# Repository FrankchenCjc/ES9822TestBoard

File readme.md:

# 关于本项目

本项目的电路设计来自ES9822的DataSheet，并使用了LM1117进行电压控制，目前版本还未进行试机

请使用kicad6.0及以上版本的kicad打开该项目
## ES9xxx符号库和器件库的问题
kicad6适用的ES9xxx的符号库还在制作，目前不打算开源

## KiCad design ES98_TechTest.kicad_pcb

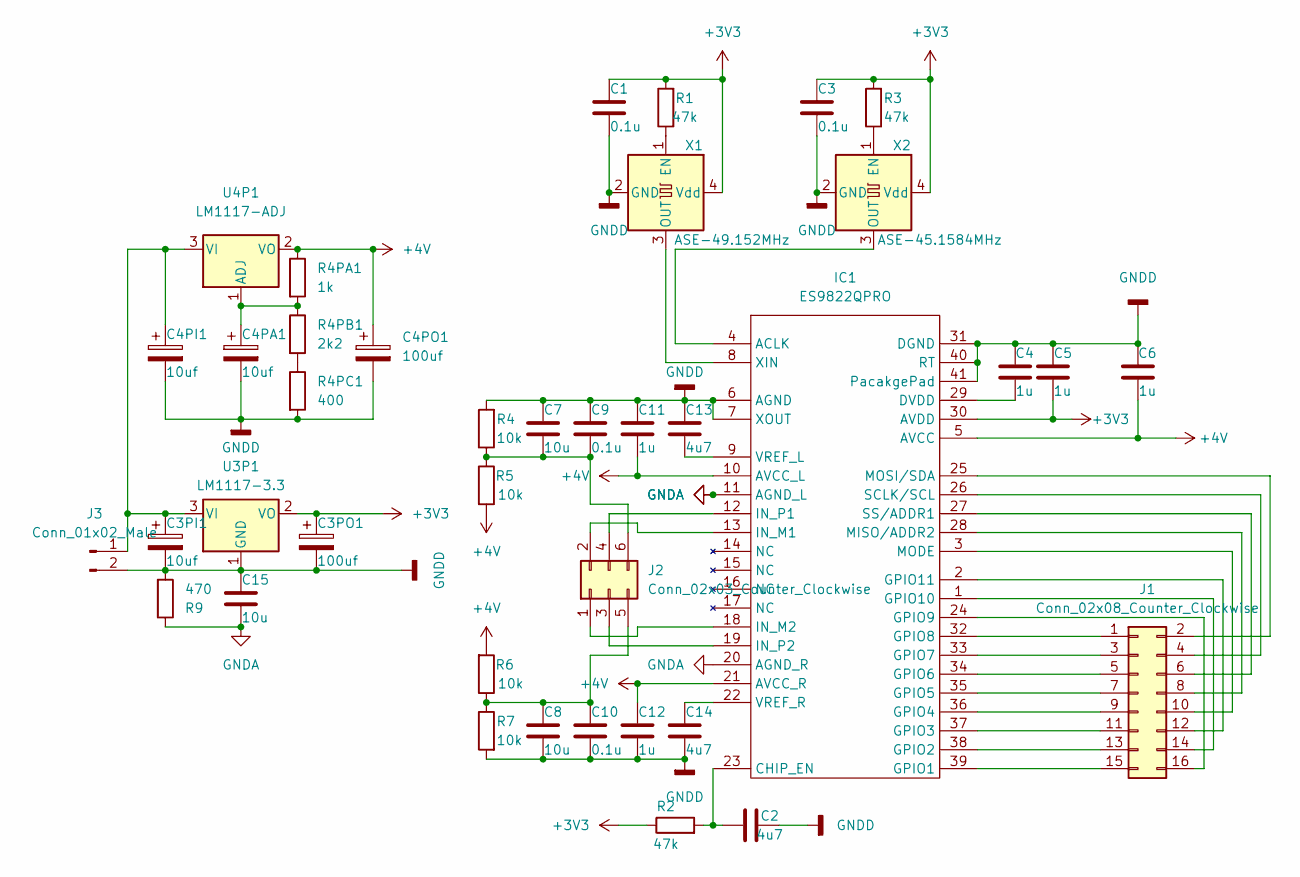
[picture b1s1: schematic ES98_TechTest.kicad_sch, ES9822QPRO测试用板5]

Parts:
C1, C3, C9, C10: 0.1u; C_0603_1608Metric_Pad1.08x0.95mm_HandSolder
C2, C13, C14: 4u7; C_0603_1608Metric_Pad1.08x0.95mm_HandSolder
C3PI1, C4PA1, C4PI1: 10uf; CP_EIA-3528-21_Kemet-B_Pad1.50x2.35mm_HandSolder
C3PO1, C4PO1: 100uf; CP_EIA-3528-21_Kemet-B_Pad1.50x2.35mm_HandSolder
C4, C5, C6, C11, C12: 1u; C_0603_1608Metric_Pad1.08x0.95mm_HandSolder
C7, C8, C15: 10u; C_0603_1608Metric_Pad1.08x0.95mm_HandSolder
IC1: ES9822QPRO; QFN-40-1EP_5x5mm_P0.4mm_EP3.8x3.8mm
J1: Conn_02x08_Counter_Clockwise; PinHeader_2x08_P2.54mm_Vertical
J2: Conn_02x03_Counter_Clockwise; PinSocket_2x03_P2.54mm_Vertical
J3: Conn_01x02_Male; PinHeader_1x02_P2.54mm_Vertical
R1, R2, R3: 47k; R_0603_1608Metric_Pad0.98x0.95mm_HandSolder
R4, R5, R6, R7: 10k; R_0603_1608Metric_Pad0.98x0.95mm_HandSolder
R4PA1: 1k; R_0603_1608Metric_Pad0.98x0.95mm_HandSolder
R4PB1: 2k2; R_0603_1608Metric_Pad0.98x0.95mm_HandSolder
R4PC1: 400; R_0603_1608Metric_Pad0.98x0.95mm_HandSolder
R9: 470; R_0603_1608Metric_Pad0.98x0.95mm_HandSolder
U3P1: LM1117-3.3; SOT-223-3_TabPin2
U4P1: LM1117-ADJ; SOT-223-3_TabPin2
X1: ASE-49.152MHz; Oscillator_SMD_Abracon_ASE-4Pin_3.2x2.5mm
X2: ASE-45.1584MHz; Oscillator_SMD_Abracon_ASE-4Pin_3.2x2.5mm

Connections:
+3V3: C1.2, C3.2, C3PO1.1, C5.1, IC1.30 (AVDD), R1.2, R2.1, R3.2, U3P1.2 (VO), X1.4 (Vdd), X2.4 (Vdd)
+4V: C4PO1.1, C6.1, C11.2, C12.1, IC1.5 (AVCC), IC1.10 (AVCC_L), IC1.21 (AVCC_R), R4PA1.1, R5.2, R6.2, U4P1.2 (VO)
GNDA: C15.1, IC1.11 (AGND_L), IC1.20 (AGND_R), R9.1
GNDD: C1.1, C2.2, C3.1, C3PI1.2, C3PO1.2, C4.2, C4PA1.2, C4PI1.2, C4PO1.2, C5.2, C6.2, C7.1, C8.1, C9.1, C10.1, C11.1, C12.2, C13.2, C14.2, C15.2, IC1.6 (AGND), IC1.7 (XOUT), IC1.31 (DGND), IC1.40 (RT), IC1.41 (PacakgePad), J3.2, R4.2, R4PC1.2, R7.2, R9.2, U3P1.1 (GND), X1.2 (GND), X2.2 (GND)
unnamed: C2.1, IC1.23 (CHIP_EN), R2.2
unnamed: C4.1, IC1.29 (DVDD)
unnamed: C7.2, C9.2, J2.6, R4.1, R5.1
unnamed: C8.2, C10.2, J2.5, R6.1, R7.1
unnamed: C13.1, IC1.9 (VREF_L)
unnamed: C14.1, IC1.22 (VREF_R)
unnamed: IC1.1 (GPIO10), J1.14
unnamed: IC1.2 (GPIO11), J1.12
unnamed: IC1.3 (MODE), J1.10
unnamed: IC1.4 (ACLK), X2.3 (OUT)
unnamed: IC1.8 (XIN), X1.3 (OUT)
unnamed: IC1.12 (IN_P1), J2.4
unnamed: IC1.13 (IN_M1), J2.2
unnamed: IC1.18 (IN_M2), J2.1
unnamed: IC1.19 (IN_P2), J2.3
unnamed: IC1.24 (GPIO9), J1.16
unnamed: IC1.25 (MOSI/SDA), J1.2
unnamed: IC1.26 (SCLK/SCL), J1.4
unnamed: IC1.27 (SS/ADDR1), J1.6
unnamed: IC1.28 (MISO/ADDR2), J1.8
unnamed: IC1.32 (GPIO8), J1.1
unnamed: IC1.33 (GPIO7), J1.3
unnamed: IC1.34 (GPIO6), J1.5
unnamed: IC1.35 (GPIO5), J1.7
unnamed: IC1.36 (GPIO4), J1.9
unnamed: IC1.37 (GPIO3), J1.11
unnamed: IC1.38 (GPIO2), J1.13
unnamed: IC1.39 (GPIO1), J1.15
unnamed: R1.1, X1.1 (EN)
unnamed: R3.1, X2.1 (EN)
unnamed: R4PB1.2, R4PC1.1
unnamed: C4PA1.1, R4PA1.2, R4PB1.1, U4P1.1 (ADJ)
unnamed: C3PI1.1, C4PI1.1, J3.1, U3P1.3 (VI), U4P1.3 (VI)

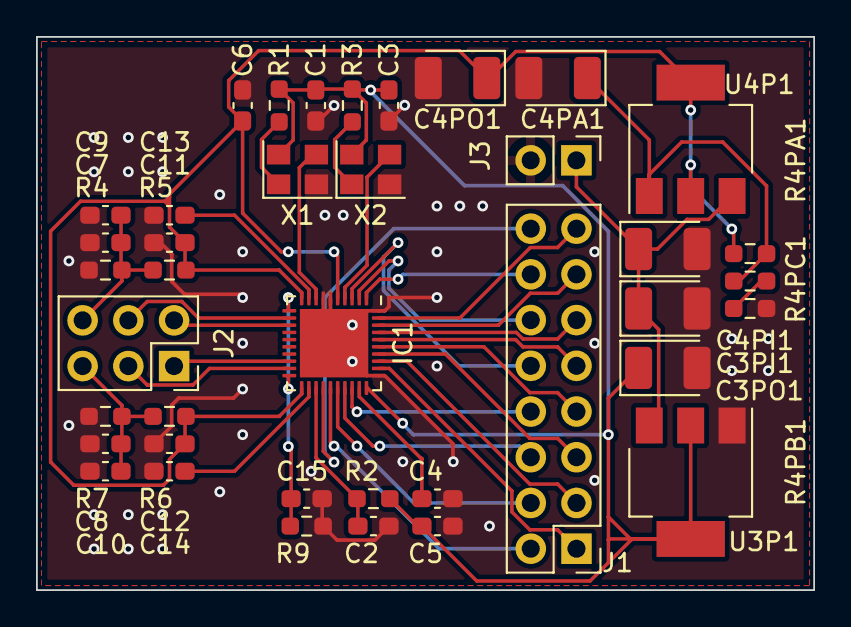
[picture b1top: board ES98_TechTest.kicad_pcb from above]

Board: 2 copper layers, 43.2 x 30.7 mm, 39 parts (0 on the bottom side), 37 nets.

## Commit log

2022-02-26 初步的版本发布
2022-02-26 添加了readme
